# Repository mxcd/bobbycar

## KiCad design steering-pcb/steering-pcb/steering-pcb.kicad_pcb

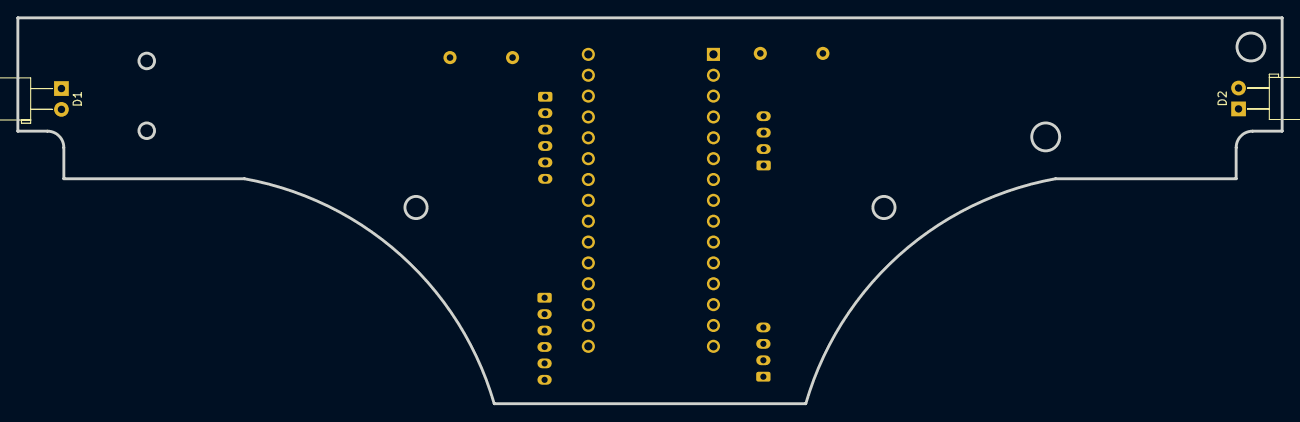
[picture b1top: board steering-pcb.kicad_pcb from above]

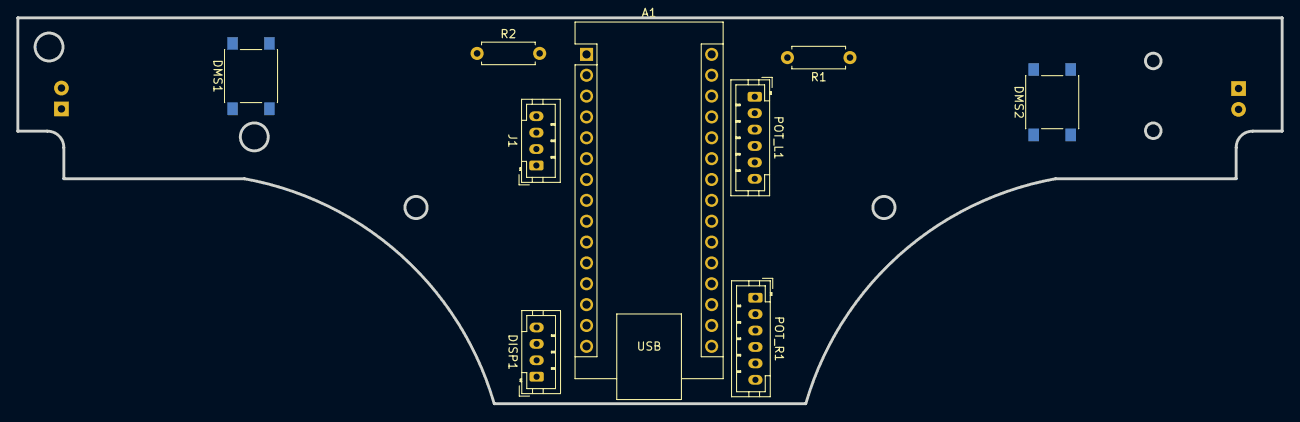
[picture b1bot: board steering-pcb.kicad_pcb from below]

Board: 2 copper layers, 154.0 x 47.0 mm, 11 parts (9 on the bottom side), 18 nets, no tracks yet.

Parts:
A1: Arduino_Nano_v3.x; Arduino_Nano
D1, D2: LED; LED_D5.0mm_Horizontal_O3.81mm_Z3.0mm
DISP1: Conn_01x04_Pin; JST_PH_B4B-PH-K_1x04_P2.00mm_Vertical
DMS1, DMS2: SW_Push; SW_SPST_PTS645
J1: Conn_01x04_Pin; JST_PH_B4B-PH-K_1x04_P2.00mm_Vertical
POT_L1: Conn_01x06_Pin; JST_PH_B6B-PH-K_1x06_P2.00mm_Vertical
POT_R1: Conn_01x06_Pin; JST_PH_B6B-PH-K_1x06_P2.00mm_Vertical
R1, R2: 56R; R_Axial_DIN0207_L6.3mm_D2.5mm_P7.62mm_Horizontal

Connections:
/5V: A1.27 (+5V), DISP1.1, J1.1, POT_L1.1, POT_R1.1
/BTN6: A1.11 (D8), POT_L1.6
/BTN7: A1.12 (D9), POT_R1.6
/DMS: A1.5 (D2), DMS1.2, DMS2.2
/LED_LEFT: A1.15 (D12), R1.2
/LED_RIGHT: A1.16 (D13), R2.2
/NRESET: A1.3 (~RESET), A1.28 (~RESET)
/POT_L_X: A1.20 (A1), POT_L1.4
/POT_L_Y: A1.19 (A0), POT_L1.3
/POT_R_X: A1.22 (A3), POT_R1.4
/POT_R_Y: A1.21 (A2), POT_R1.3
/RX: A1.2 (D0/RX), J1.3
/SCL: A1.24 (A5), DISP1.4
/SDA: A1.23 (A4), DISP1.3
/TX: A1.1 (D1/TX), J1.4
GND: A1.4 (GND), A1.29 (GND), D1.1 (K), D2.1 (K), DISP1.2, DMS1.1, DMS2.1, J1.2, POT_L1.2, POT_L1.5, POT_R1.2, POT_R1.5
unnamed: D1.2 (A), R1.1
unnamed: D2.2 (A), R2.1

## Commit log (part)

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2024-03-04 feat: driving bobbycar
2024-03-04 fix: ensuring vd command is zero unless vehicle state is MC_ACTIVE
2025-07-01 feat: adding steering pcb
2025-07-12 add unit info
2025-07-12 add battery voltage check to safetyCheck
2025-07-15 battery voltage ok default and checked when TS active
2026-04-14 feat: vesc including undervoltage protection
